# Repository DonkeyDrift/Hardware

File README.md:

# MUS4 硬件设计 - v1.0.0

> 一台能跑神经网络的小车，一个能上手的自动驾驶课堂。
>
> MUS4 面向 AI 极客、RC 车手与教育工作者，基于 DonkeyCar / 漂移驴车开源生态打造，融合 LattePanda MU 上位机算力与 ESP32 下位机控制，以纯视觉感知、云端模型训练与一键部署，让每个人都能快速搭建属于自己的端到端自动驾驶小车。

***

## 项目概述

这是 MUS4 自动驾驶小车的硬件设计仓库，包含 KiCad 格式的原理图和 PCB 布局文件。

### 硬件特性

- **LattePanda MU 主控接口**：支持上位机算力模块
- **ESP32 下位机驱动电路**：实时底层运动控制
- **摄像头、电机、舵机、传感器接口**：丰富的外设扩展
- **电源管理与电池监测电路**：安全可靠的供电系统
- **通信接口**：USB / 串口 / I2C / PWM
- **支持直接导出 Gerber 生产文件**：方便 PCB 打样

### 设计文件

| 文件名                           | 描述                |
| ----------------------------- | ----------------- |
| `DonkeyDrift-MUS4.kicad_pro`  | KiCad 项目文件        |
| `DonkeyDrift-MUS4.kicad_sch`  | 原理图文件             |
| `DonkeyDrift-MUS4.kicad_pcb`  | PCB 布局文件          |
| `Controller.kicad_sch`        | 控制器子原理图           |
| `ESP32.kicad_sch`             | ESP32 子原理图        |
| `HDMI.kicad_sch`              | HDMI 接口子原理图       |
| `Interface.kicad_sch`         | 接口子原理图            |
| `LattePanda Module.kicad_sch` | LattePanda 模块子原理图 |
| `M.2 E&amp;M Key.kicad_sch`   | M.2 接口子原理图        |
| `PSU.kicad_sch`               | 电源子原理图            |
| `USB2.0&amp;USB3.0.kicad_sch` | USB 接口子原理图        |

### 目录结构

```
Hardware/
├── BOM/              # 物料清单文件夹
├── Drill/            # 钻孔文件文件夹
├── Gerber/           # Gerber 生产文件文件夹
├── Layout/           # PCB 布局图片文件夹
├── kicad_api_libs/   # KiCad 库文件
└── [主设计文件]      # KiCad 项目、原理图、PCB 文件
```

***

## 为什么选择 MUS4

- **纯视觉端到端架构**：无需激光雷达、高精地图等昂贵传感器，仅凭摄像头即可完成感知与决策
- **双核协同，分工明确**：LattePanda MU（Ubuntu + Python）负责图像感知与模型推理，ESP32（Arduino C++）负责实时底层运动控制
- **一站式硬件平台**：自研 PCB 板打通上下位机通信，无需从零焊接飞线
- **全栈开源，社区共建**：硬件设计、软件代码、训练模型全面开源

***

## 快速开始

### 1. 查看设计文件

使用 KiCad 10.0 或更高版本打开项目文件：

```bash
# 克隆仓库
git clone <your-repo-url>
cd Hardware

# 用 KiCad 打开项目
kiCad DonkeyDrift-MUS4.kicad_pro
```

### 2. 导出 Gerber 文件

1. 在 KiCad PCB Editor 中打开 `DonkeyDrift-MUS4.kicad_pcb`
2. 点击 `File` → `Plot`
3. 选择输出格式为 Gerber
4. 配置各层输出设置
5. 点击 `Plot` 生成 Gerber 文件
6. 生成钻孔文件：`File` → `Fabrication Outputs` → `Drill Files`

### 3. 查看 BOM

物料清单位于 `BOM/` 文件夹中。

### 4. 生产文件

- Gerber 文件已导出到 `Gerber/` 文件夹
- 钻孔文件已导出到 `Drill/` 文件夹

***

## 项目架构

MUS4 硬件系统采用上下位机架构：

```
┌─────────────────────────────────────────┐
│         LattePanda MU (上位机)          │
│  - Ubuntu Linux                         │
│  - Python / OpenCV / TensorFlow         │
│  - 图像采集与模型推理                   │
└──────────────┬──────────────────────────┘
               │ USB/串口通信
┌──────────────▼──────────────────────────┐
│         ESP32 (下位机)                  │
│  - Arduino C++                          │
│  - 实时运动控制                         │
│  - 电机/舵机驱动                        │
│  - 传感器读取                           │
└──────────────┬──────────────────────────┘
               │
┌──────────────▼──────────────────────────┐
│         外设接口                         │
│  - 摄像头                               │
│  - 电机 / 舵机                          │
│  - 电池管理                             │
│  - 其他传感器                           │
└─────────────────────────────────────────┘
```

***

## 相关资源

- **主代码库**：[https://github.com/DonkeyDrift](https://github.com/DonkeyDrift/DonkeyDrift)
  - 软件库：<https://github.com/DonkeyDrift/DonkeyDrift>
  - 固件库：<https://github.com/DonkeyDrift/Firmware>
  - 硬件库：<https://github.com/DonkeyDrift/Hardware>
- **产品指南**：\[待补充]
- **3D 打印模型**：\[待补充]
- **DonkeyDrift 社区**：[donkeydrift.com](https://www.donkeydrift.com)

***

## 一台小车，七种能力

MUS4 不仅是一台自动驾驶小车，更是一套全栈式的学习平台：

- **Linux 操作系统**：系统管理、环境配置、服务部署
- **Python 编程**：图像处理、数据采集、模型推理
- **神经网络与机器学习**：端到端自动驾驶模型训练
- **计算机视觉**：OpenCV 图像处理、车道线识别
- **单片机与嵌入式开发**：ESP32 编程、Arduino C++
- **多协议处理**：USB、串口、I2C、PWM 等硬件协议
- **RC 赛车技术**：车架结构、电机调校、转向微调

***

## 开源协议（v1.1 · 分层授权）

本仓库按**客体分层授权**，自社区委员会《开源许可证分层授权决议》生效之日起适用：

| 客体 | 许可证 | 全文 |
| --- | --- | --- |
| 本仓库硬件设计文件（原理图、PCB、封装库、Gerber、钻孔、BOM、结构图、Layout 图）及其衍生实物 | **CERN Open Hardware Licence Version 2 - Permissive（CERN-OHL-P-2.0）** | [LICENSE](LICENSE) |
| 配套固件与软件（`Firmware` 仓库 MUS4_FW、上位机代码） | **Apache License 2.0** | 见 `Firmware` 仓库根目录 `LICENSE` |
| 文档与课程资料 | 逐项单独标注 | 含 CC BY-NC 等非商业限制的材料不随开源包分发，仅外链并注明 |

- **变体必须写全**：CERN-OHL-P-2.0 第 7.3 条规定，未写明变体会被默认按 CERN-OHL-S（强互惠）解释；所有对外声明一律使用 `CERN-OHL-P-2.0 / Version 2 - Permissive` 全称。
- **商标与认证**：两个协议都不授予「漂移驴车 / DonkeyDrift」名称、Logo、商标或「官方认证套件」资格，使用须经社区委员会书面批准，非官方版本须标注「非官方认证」。
- **生效边界**：Apache-2.0 授权不可撤销。此前已按 Apache-2.0 取得本设计的接收方，其已获授权不追溯变更；历史全文存档于 [LICENSE-Apache-2.0.archive.txt](LICENSE-Apache-2.0.archive.txt)。
- **版权主体与 Notice**：详见 [NOTICE.md](NOTICE.md)；最终署名以社区委员会书面决议为准。

完整发布口径与四处一致性检查见《漂移驴车-华秋开源发布准备方案》v1.1 第 4.2、4.7 节。

***

## 社区与贡献

漂移驴车社区邀请所有热爱技术、勇于创新的你加入！

- **问题反馈**：提交 Issue
- **贡献指南**：欢迎提交 Pull Request
- **联系方式**：<contact@donkeydrift.com>

***

> 因为热爱，所以极致。
>
> **漂移驴车社区，与您一同驶向智能车的未来！**

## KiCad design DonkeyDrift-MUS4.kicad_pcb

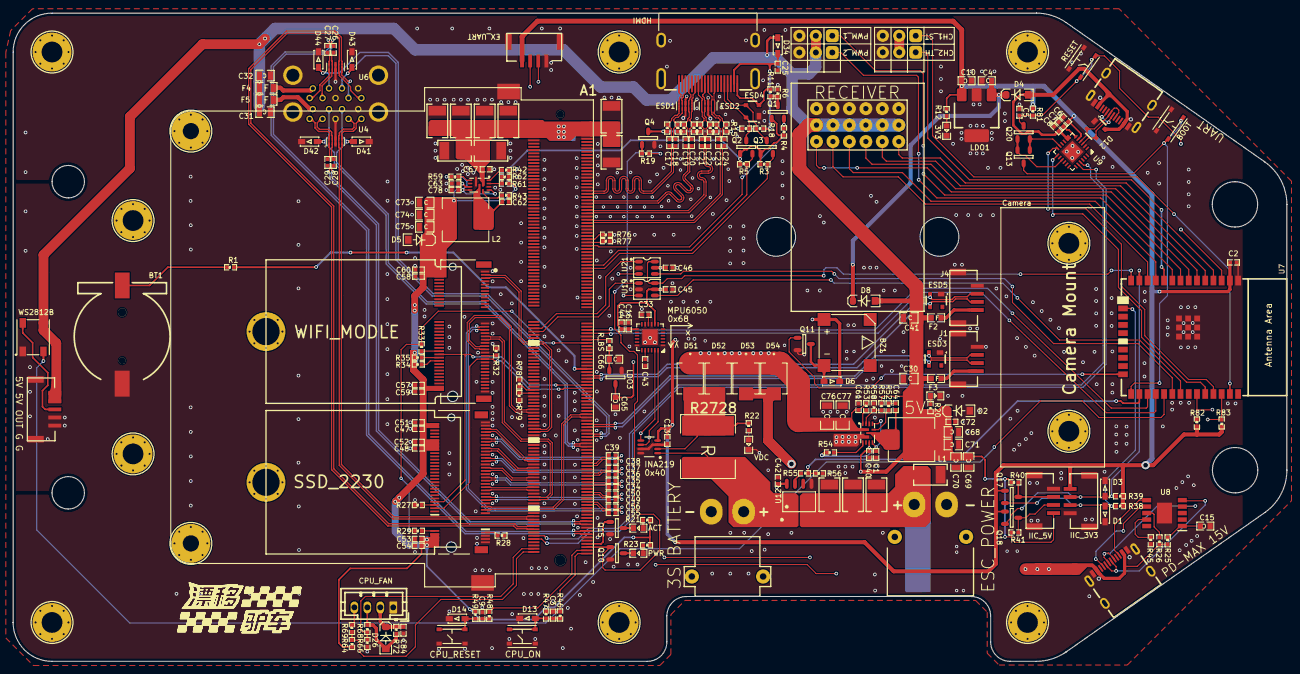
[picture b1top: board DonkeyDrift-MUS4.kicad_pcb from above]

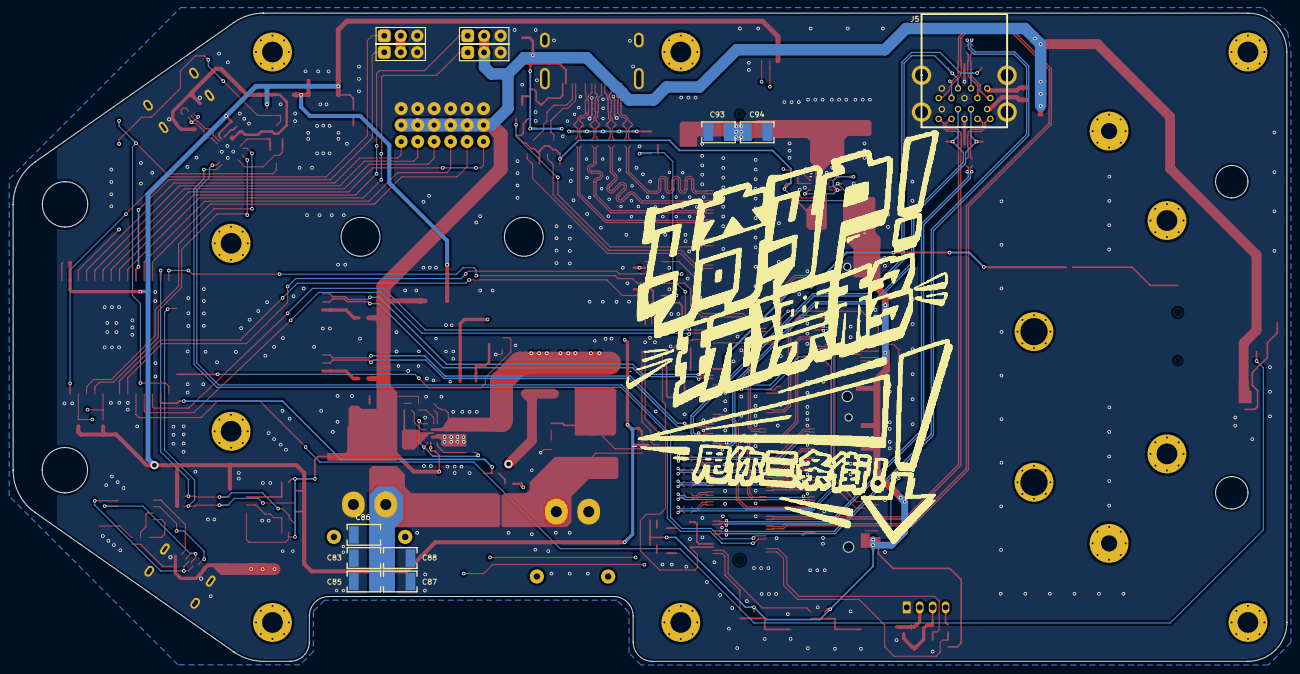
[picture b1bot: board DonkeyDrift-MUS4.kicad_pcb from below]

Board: 4 copper layers, 196.5 x 100.0 mm, 261 parts (12 on the bottom side), 198 nets.

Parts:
0x40: INA219AxD; SOT-23-8
0x68: MPU-6050; QFN-24-4X4-PAD
3S BATTERY: Conn_01x02_Pin; XT30PW-M
3V3, 5V: LED_Y; LED-0603-Y
5V 5V OUT G G: Conn_01x05_Socket; GH1.25-立-5P
A1: ASAA826-E8SB0-7H; LattePanda_Module_H8.0mm_Horizontal
ACT: LED_R; LED-0603-R
BOOT: SW_Push; SWITCH-3*4*2.5
BT1: XDCR-1220-006; Battery_Holder_CR1220_S8411-45R
BZ1: Buzzer; BEEP-MLT-8530
C1: 25V/1uf; C-0402
C2, C7, C8, C16, C17, C18, C19, C20, C21, C22, C23, C24, C25, C26, C27, C28, C29, C33, C40, C45, C46, C47, C48, C54, C59, C60, C61, C63, C67, C72, C84: 50V/100nf; C-0402
C3, C5, C6, C9, C44, C51, C52, C53, C57, C58, C78: 10V/1uf; C-0402
C4, C10: 10V/10uf; C-0603
C13, C42: 50V/100pf; C-0402
C15, C65, C66: 25V/1uf; C-0603
C30, C31, C32, C41, C68, C69, C70, C71, C73, C74, C75: 16V/22uf; C-0805
C34, C35, C36, C37, C38, C39, C49, C50, C55, C56, C62, C64: 50V/220nf; C-0402
C43: 50V/2.2nf; C-0402
C76, C77: 25V/22uf; C-1206
C80, C81, C82, C83, C85, C86, C87, C88, C89, C90, C91, C92, C93, C94, C95, C96, C97, C98, C99: 25V/47uf; C-1210
CH1_ST, CH2_TH: Conn_01x03_Socket; J-2.54-1X3
CPU_FAN: Fan_4pin; JST_PH_B4B-PH-K_1x04_P2.00mm_Vertical
CPU_ON: SW_Push; SWITCH-3*4*2.5
CPU_RESET: SW_Push; SWITCH-3*4*2.5
Camera: 摄像头; Camera Mount
D1, D3, D13, D14: ESD5V0B03; SOD-323
D2, D5: SMFJ5.0CA; SOD-123
D4, D8, D26: 1N5819WS; SOD-123
D6: 1N4148WS; SOD-323
D12: SP0503BAHT; SOT-143
D34: 1N5819WS; SOD-323
D41, D42, D43, D44: ESD-5V0B03; SOD-323
D51, D52, D53, D54: SL54B; c167b71becf44403bc24886c573a5209
DCDC1, DCDC2: MP8756GD; QFN-12-MP8756
ESC_POWER: 电调供电; XT30PW-F
ESD1, ESD2: TPAZ1023-04F; ESD-USON-10_0P5_2P5X1X0P55MM
ESD3, ESD4, ESD5: SP0503BAHT; SOT-143
EX_UART: Conn_01x04_Socket; GH1.25-立-4P
F2, F3: 6V/500mA; FUSE-0603
F4, F5: 6V/1A; FUSE-0805
FID1, FID2, FID3, FID4, FID5, FID6, FID7, FID8: Fiducial; 铜柱
HDMI: HDMI_A
IIC_3V3, IIC_5V: Conn_01x04_Socket; GH1.25-立-4P
J1, J4: Conn_01x04_Socket; GH1.25-立-4P
J5: USB3_A; USB3_A_HanElctricity
L1, L2: 3.3uH/5.2A; L-0630
LDO1: SGM2225-3.3XKC3G/TR; SOT-223-3_TabPin2
LDO3: LDO-XC6206P332MR; SOT-23-3
LOGO: LOGO-2
LOGO3: LOGO-3
PD-MAX 15V: USB_C_Receptacle_USB2.0_16P; USB-C-16P
PWM_1, PWM_2: Conn_01x03_Socket; J-2.54-1X3
PWR: LED_G; LED-0603-G
Q1, Q2, Q3, Q4, Q10, Q11, Q15, Q17, Q18: AO3400A; SOT-23-3
Q13, Q20: 2N7002; SOT-23-3
R1: 750; R-0402
R3, R5, R12, R15, R18, R19, R21, R23: 2.2K; R-0402
R4, R42, R53: 1M; R-0402
R6, R68: 21.5K; R-0402
R7, R8, R9, R10, R13, R14, R16, R17, R56: 470R; R-0402
R11: 1K; R-0402
R20, R72: 4.7K; R-0402
R22: 18K; R-0402
R25: 1K 1%; R-0402
R26: 10K 1%; R-0402
R27, R29, R32, R33: 0R; R-0402
R28, R47, R49, R64, R66: NC; R-0402
R34, R35, R78, R79, R81: 10K; R-0402
R38, R39, R82, R83: 3.3K; R-0402
R40, R41: 5.1K; R-0402
R43, R52: 3.3R; R-0402
R45: 56K 1%; R-0402
R46, R48, R69: 100R; R-0402
R54, R59, R76, R77: 100K; R-0402
R55: 680R; R-0402
R57: 41.2K; R-0402
R58: 5.6K; R-0402
R61: 43K; R-0402
R62: 9.53K; R-0402
R2728: 0.01R; R-2728
RECEIVER: RC_MODULE; RC_INTERFACE
RESET: SW_Push; SWITCH-3*4*2.5
R_BS: 10K; R-0402
SSD_2230: APCI0079-P002A; PCIE_M.2_CONNECTORS_P=0.5MM_H=4.2MM_KEYM
U4, U6: ULC0524P; ESD-USON-10_0P5_2P5X1X0P55MM
U7: ESP32-WROOM-32E-N4; ESP32-WROOM-32E
U8: CH224K; SOP100P600X180-11N
U9: CH342F; QFN-24-4X4-PAD
U12: CC6900SO; SOP-8
U19, U21: TS5A3159ADBVR; SOT-23-6
UART: USB_C_Receptacle_USB2.0_16P; USB-C-16P
VDC: LED_R; LED-0603-R
WIFI_MODLE: APCI0085-P005A; PCIE_M.2_CONNECTORS_P=0.5MM_H=4.2MM_KEYE
WS2812B: LED-WS2812B; LED-5050-4P

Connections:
5V_HDMI_VCC: C25.2, D34.1, HDMI.18, R15.2, R18.2
+3V3: 0x40.4, 0x68.8, 0x68.13, BZ1.1, C2.1, C6.2, C10.2, C13.2, C16.2, C44.2, C45.2, C46.2, D6.1, EX_UART.1, IIC_3V3.1, LDO1.3, Q17.1, Q18.1, R12.2, R38.2, R39.2, R81.2, R82.1, R83.2, U7.2, U9.5, U19.5, U21.5
+3V3C: C47.1, C48.2, C51.1, C52.1, C53.1, C54.2, C57.1, C58.1, C59.1, C60.1, R34.2, R35.2, SSD_2230.2, SSD_2230.4, SSD_2230.12, SSD_2230.14, SSD_2230.16, SSD_2230.18, SSD_2230.70, SSD_2230.72, SSD_2230.74, WIFI_MODLE.2, WIFI_MODLE.4, WIFI_MODLE.72, WIFI_MODLE.74
+5V: 5V 5V OUT G G.4, 5V 5V OUT G G.5, C30.2, C31.2, C32.2, C40.2, C41.2, C42.2, C68.2, C69.2, C70.2, C71.2, C72.2, C84.2, CPU_FAN.2, D2.1, D8.2, D26.1, D34.2, DCDC1.5, F2.1, F3.1, F4.1, F5.1, IIC_5V.1, L1.2, PWM_1.2, PWM_2.2, R20.2, R40.2, R41.2, R57.2, R72.2, RECEIVER.7, U12.8, WS2812B.1
+5V_USB: C8.2, D4.2, D12.4, U9.7, U9.8, UART.A4
+BATT: A1.115, R1.1
BEC_5V: CH1_ST.2, CH2_TH.2
BOOT: BOOT.1, Q13.3, U7.25
BZ: Q11.1, U7.24
CHIP_PU: C5.2, Q20.3, R81.1, RESET.2, U7.3
CON_PCIE_TX_0_N: C56.2, WIFI_MODLE.37
CON_PCIE_TX_0_P: C55.2, WIFI_MODLE.35
CON_PCIE_TX_1_N: C50.2, SSD_2230.47
CON_PCIE_TX_1_P: C49.2, SSD_2230.49
CON_PCIE_TX_2_N: C35.2, SSD_2230.35
CON_PCIE_TX_2_P: C34.2, SSD_2230.37
CON_PCIE_TX_3_N: C37.2, SSD_2230.23
CON_PCIE_TX_3_P: C36.2, SSD_2230.25
CON_PCIE_TX_4_N: C39.2, SSD_2230.11
CON_PCIE_TX_4_P: C38.2, SSD_2230.13
CPU_RX0: A1.12, U9.21
CPU_RX2: A1.140, U21.1
CPU_TX0: A1.10, U9.20
CPU_TX2: A1.138, U19.1
DDC_SCL: ESD4.4, HDMI.15, Q2.3, R15.1
DDC_SDA: ESD4.3, HDMI.16, Q3.3, R18.1
DDI_B_TX0_N: A1.215, C18.1
DDI_B_TX0_P: A1.217, C17.1
DDI_B_TX1_N: A1.209, C20.1
DDI_B_TX1_P: A1.211, C19.1
DDI_B_TX2_N: A1.203, C22.1
DDI_B_TX2_P: A1.205, C21.1
DDI_B_TX3_N: A1.197, C24.1
DDI_B_TX3_P: A1.199, C23.1
DTR: Q13.2, Q20.1, U9.15
EX_RX: EX_UART.3, U19.3
EX_TX: EX_UART.2, U21.3
FAN_1_PWM: A1.2, R64.1, R69.1
FAN_1_TAC: A1.4, R66.2, R68.2
GND: 0x40.3, 0x40.7, 0x40.8, 0x68.1, 0x68.9, 0x68.11, 0x68.18, 0x68.25, 3S BATTERY.2, 3V3.1, 5V.1, 5V 5V OUT G G.1, 5V 5V OUT G G.2, 5V 5V OUT G G.MP, A1.11, A1.14, A1.17, A1.20, A1.23, A1.26, A1.29, A1.32, A1.35, A1.38, A1.41, A1.44, A1.47, A1.50, A1.53, A1.56, A1.59, A1.62, A1.65, A1.68, A1.71, A1.74, A1.77, A1.80, A1.83, A1.86, A1.89, A1.92, A1.95, A1.98, A1.101, A1.107, A1.110, A1.113, A1.116, A1.135, A1.136, A1.151, A1.158, A1.167, A1.170, A1.181, A1.182, A1.188, A1.189, A1.194, A1.195, A1.200, A1.201, A1.206, A1.207, A1.212, A1.213, A1.218, A1.219, A1.224, A1.225, A1.230, A1.231, A1.236, A1.237, A1.242, A1.243, A1.248, A1.249, A1.MP, BOOT.2, BT1.2, C1.1, C2.2, C3.1, C4.1, C5.1, C6.1, C7.1, C8.1, C9.1, C10.1, C13.1, C15.1, C16.1, C25.1, C30.1, C31.1, C32.1, C33.1, C40.1, C41.1, C42.1, C43.2, C44.1, C45.1, C46.1, C47.2, C48.1, C51.2, C52.2, C53.2, C54.1, C57.2, C58.2, C59.2, C60.2, C61.1, C63.1, C65.1, C66.2, C67.1, C68.1, C69.1, C70.1, C71.1, C72.1, C73.1, C74.1, C75.1, C76.1, C77.1, C78.1, C80.1, C81.1, C82.1, C83.1, C84.1, C85.1, C86.2, C87.2, C88.2, C89.2, C90.2, C91.2, C92.2, C93.2, C94.2, C95.1, C96.1, C97.1, C98.1, C99.1, CH1_ST.3, CH2_TH.3, CPU_FAN.1, CPU_ON.2, CPU_RESET.2, D1.1, D2.2, D3.1, D5.2, D12.1, D13.1, D14.1, D41.1, D42.1, D43.1, D44.1, DCDC1.2, DCDC1.10, DCDC2.2, DCDC2.10, ESC_POWER.2, ESD1.3, ESD1.8, ESD2.3, ESD2.8, ESD3.1, ESD4.1, ESD5.1, EX_UART.4, EX_UART.MP, HDMI.2, HDMI.5, HDMI.8, HDMI.11, HDMI.17, HDMI.SH, IIC_3V3.4, IIC_3V3.MP, IIC_5V.4, IIC_5V.MP, J1.4, J1.MP, J4.4, J4.MP, J5.4, J5.7, J5.13, J5.16, J5.19, LDO1.2, LDO1.4, LDO3.1, PD-MAX 15V.A1, PD-MAX 15V.S1, PWM_1.3, PWM_2.3, Q4.2, Q10.2, Q11.2, Q15.2, R6.1, R27.2, R28.2, R32.2, R45.1, R56.1, R58.1, R62.1, R66.1, R76.1, R77.1, R78.1, R79.1, RECEIVER.8, RESET.1, SSD_2230.1, SSD_2230.3, SSD_2230.9, SSD_2230.15, SSD_2230.21, SSD_2230.27, SSD_2230.33, SSD_2230.38, SSD_2230.39, SSD_2230.45, SSD_2230.51, SSD_2230.57, SSD_2230.71, SSD_2230.73, SSD_2230.75, U4.3, U4.8, U6.3, U6.8, U7.1, U7.39, U8.11, U9.2, U9.25, U12.5, U19.2, U21.2, UART.A1, UART.S1, VDC.1, WIFI_MODLE.1, WIFI_MODLE.7, WIFI_MODLE.18, WIFI_MODLE.33, WIFI_MODLE.39, WIFI_MODLE.45, WIFI_MODLE.51, WIFI_MODLE.57, WIFI_MODLE.63, WIFI_MODLE.69, WIFI_MODLE.75, WS2812B.3
HPD: ESD4.2, HDMI.19, R11.2
ID_MOTO: R55.2, R56.2, U7.26
J1_USB_2_P5_N: A1.109, ESD5.3, J4.2
J1_USB_2_P5_P: A1.111, ESD5.2, J4.3
J4_USB_2_P3_N: A1.79, ESD3.3, J1.2
J4_USB_2_P3_P: A1.81, ESD3.2, J1.3
J5_USB3_SSRX_N: A1.18, J5.5, U6.4, U6.7
J5_USB3_SSRX_P: A1.16, J5.6, U6.5, U6.6
J5_USB3_SSTX_N: C26.2, J5.8, U6.2, U6.9
J5_USB3_SSTX_P: C27.2, J5.9, U6.1, U6.10
J5_USB_2_P2_N: A1.73, D44.2, J5.2
J5_USB_2_P2_P: A1.75, D43.2, J5.3
J6_USB4_SSRX_N: A1.24, J5.14, U4.5, U4.6
J6_USB4_SSRX_P: A1.22, J5.15, U4.4, U4.7
J6_USB4_SSTX_N: C28.2, J5.17, U4.2, U4.9
J6_USB4_SSTX_P: C29.2, J5.18, U4.1, U4.10
J6_USB_2_P1_N: A1.67, D42.2, J5.11
J6_USB_2_P1_P: A1.69, D41.2, J5.12
MCU_RX0: U7.34, U9.13
MCU_RX2: U7.31, U19.4
MCU_TX0: U7.35, U9.12
MCU_TX2: U7.30, U21.4
Net3V3_2: 3V3.2, R12.1
Net5V 5V OUT G G_3: 5V 5V OUT G G.3, WS2812B.2
Net5V_2: 5V.2, R20.1
NetA1_1: A1.1, R46.1
NetA1_3: A1.3, R48.1
NetA1_5: A1.5, Q10.1
NetA1_7: A1.7, Q15.1
NetA1_100: A1.100, R79.2
NetA1_102: A1.102, R78.2
NetA1_131: A1.131, R29.2, R33.2
NetA1_133: A1.133, R_BS.1
NetA1_137: A1.137, U7.28
NetA1_139: A1.139, U7.27
NetA1_169: A1.169, Q3.2, R3.1
NetA1_171: A1.171, Q2.2, R5.1
NetA1_183: A1.183, Q1.2, R4.1
NetA1_185: A1.185, R77.2
NetA1_187: A1.187, R76.2
NetBT1_1: BT1.1, R1.2
NetBZ1_2: BZ1.2, D6.2, Q11.3
NetC1_2: C1.2, DCDC1.6, DCDC1.9, R54.2
NetC3_2: C3.2, CPU_ON.1, D13.2, R46.2, R47.1
NetC4_2: C4.2, D4.1, D8.1, LDO1.1
NetC7_2: C7.2, U9.6
NetC9_2: C9.2, CPU_RESET.1, D14.2, R48.2, R49.1
NetC15_2: C15.2, R25.2, U8.1
NetC33_2: 0x68.10, C33.2
NetC43_1: 0x68.20, C43.1
NetC62_1: C62.1, DCDC2.7, L2.1
NetC62_2: C62.2, R43.2
NetC64_1: C64.1, DCDC1.7, L1.1
NetC64_2: C64.2, R52.2
NetC66_1: C66.1, LDO3.2, R_BS.2
NetC78_2: C78.2, DCDC2.6, DCDC2.9, R59.2
NetCH1_ST_1: CH1_ST.1, U7.37
NetCH2_TH_1: CH2_TH.1, U7.10
NetCPU_FAN_3: CPU_FAN.3, D26.2, R68.1, R72.1
NetCPU_FAN_4: CPU_FAN.4, R69.2
NetD12_2: D12.2, U9.4, UART.A7, UART.B7
NetD12_3: D12.3, U9.3, UART.A6, UART.B6
NetD53_1: D53.2, D54.2, PD-MAX 15V.A4, R25.1, R26.2
NetDCDC1_3: DCDC1.3, R54.1
NetDCDC1_8: DCDC1.8, R52.1
NetDCDC1_11: DCDC1.11, R57.1, R58.2
NetDCDC1_12: DCDC1.12, R53.1
NetDCDC2_3: DCDC2.3, R59.1
NetDCDC2_8: DCDC2.8, R43.1
NetDCDC2_11: DCDC2.11, R61.1, R62.2
NetDCDC2_12: DCDC2.12, R42.1
NetF2_2: F2.2, J4.1
NetF3_2: F3.2, J1.1
NetF4_2: F4.2, J5.1
NetF5_2: F5.2, J5.10
NetIIC_5V_2: IIC_5V.2, Q18.3, R41.1
NetIIC_5V_3: IIC_5V.3, Q17.3, R40.1
NetPD-MAX 15V_A5: PD-MAX 15V.A5, U8.7
NetPD-MAX 15V_A6: PD-MAX 15V.A6, PD-MAX 15V.B6, U8.4
NetPD-MAX 15V_A7: PD-MAX 15V.A7, PD-MAX 15V.B7, U8.5
NetPD-MAX 15V_B5: PD-MAX 15V.B5, U8.6
NetPWM_1_1: PWM_1.1, U7.8
NetPWM_2_1: PWM_2.1, U7.9
NetPWR_1: PWR.1, Q10.3
NetPWR_2: PWR.2, R23.1
NetQ1_3: Q1.3, R6.2, R11.1
NetQ4_1: Q4.1, R19.1
NetQ4_3: Q4.3, R7.1, R8.1, R9.1, R10.1, R13.1, R14.1, R16.1, R17.1
NetQ15_3: ACT.1, Q15.3
NetR21_1: ACT.2, R21.1
NetR22_1: R22.1, VDC.2
NetR26_1: R26.1, U8.8
NetR28_1: R28.1, SSD_2230.69
NetR29_1: R29.1, SSD_2230.68
NetR33_1: R33.1, WIFI_MODLE.50
NetR34_1: R34.1, WIFI_MODLE.56
NetR35_1: R35.1, WIFI_MODLE.54
NetR45_2: R45.2, U8.9
NetR55_1: R55.1, U12.7
PCIE_RX_0_N: A1.36, WIFI_MODLE.43
PCIE_RX_0_P: A1.34, WIFI_MODLE.41
PCIE_RX_1_N: A1.42, SSD_2230.41
PCIE_RX_1_P: A1.40, SSD_2230.43
PCIE_RX_2_N: A1.48, SSD_2230.29
PCIE_RX_2_P: A1.46, SSD_2230.31
PCIE_RX_3_N: A1.54, SSD_2230.17
PCIE_RX_3_P: A1.52, SSD_2230.19
PCIE_RX_4_N: A1.60, SSD_2230.5
PCIE_RX_4_P: A1.58, SSD_2230.7
PCIE_TX_0_N: A1.33, C56.1
PCIE_TX_0_P: A1.31, C55.1
PCIE_TX_1_N: A1.39, C50.1
PCIE_TX_1_P: A1.37, C49.1
PCIE_TX_2_N: A1.45, C35.1
PCIE_TX_2_P: A1.43, C34.1
PCIE_TX_3_N: A1.51, C37.1
PCIE_TX_3_P: A1.49, C36.1
PCIE_TX_4_N: A1.57, C39.1
PCIE_TX_4_P: A1.55, C38.1
PWM_IN1: RECEIVER.1, U7.4
PWM_IN2: RECEIVER.2, U7.5
PWM_IN3: RECEIVER.3, U7.6
PWM_IN4: RECEIVER.4, U7.11
PWM_IN5: RECEIVER.5, U7.12
PWM_IN6: RECEIVER.6, U7.7
REFCLKE_N: A1.90, WIFI_MODLE.49
REFCLKE_P: A1.88, WIFI_MODLE.47
REFCLKM_N: A1.87, SSD_2230.53
REFCLKM_P: A1.85, SSD_2230.55
RTS: Q13.1, Q20.2, U9.11
SCL0: 0x40.5, 0x68.23, R83.1, U7.36
SCL_3: D3.2, IIC_3V3.2, Q18.2, R39.1, U7.13
SDA0: 0x40.6, 0x68.24, R82.2, U7.33
SDA_3: D1.2, IIC_3V3.3, Q17.2, R38.1, U7.16
TMDS_CK_N: C24.2, ESD2.1, ESD2.10, HDMI.12, R7.2
TMDS_CK_P: C23.2, ESD2.2, ESD2.9, HDMI.10, R8.2
TMDS_D0_N: C22.2, ESD2.4, ESD2.7, HDMI.9, R9.2
TMDS_D0_P: C21.2, ESD2.5, ESD2.6, HDMI.7, R10.2
TMDS_D1_N: C20.2, ESD1.1, ESD1.10, HDMI.6, R13.2
TMDS_D1_P: C19.2, ESD1.2, ESD1.9, HDMI.4, R14.2
TMDS_D2_N: C18.2, ESD1.4, ESD1.7, HDMI.3, R16.2
TMDS_D2_P: C17.2, ESD1.5, ESD1.6, HDMI.1, R17.2
UART_SEL: U7.14, U19.6, U21.6
USB3_SSTX_N: A1.15, C26.1
USB3_SSTX_P: A1.13, C27.1
USB4_SSTX_N: A1.21, C28.1
USB4_SSTX_P: A1.19, C29.1
USB_2_P7_N: A1.78, WIFI_MODLE.5
USB_2_P7_P: A1.76, WIFI_MODLE.3
VCPU: A1.250, A1.251, A1.252, A1.253, A1.254, A1.255, A1.256, A1.257, A1.258, A1.259, A1.260, C61.2, C65.2, C67.2, C76.2, C77.2, C90.1, C91.1, C92.1, C93.1, C94.1, C95.2, C96.2, C97.2, C98.2, C99.2, D51.1, D52.1, D53.1, D54.1, DCDC1.1, DCDC2.1, LDO3.3, R42.2, R53.2
VDC: 0x40.2, D51.2, D52.2, R22.2, R2728.1
VIN: 0x40.1, 3S BATTERY.1, R2728.2, U12.1, U12.2
VMOTO: C80.2, C81.2, C82.2, C83.2, C85.2, C86.1, C87.1, C88.1, C89.1, ESC_POWER.1, U12.3, U12.4
WS2812: U7.29, WS2812B.4
~{CLKREQE}: R32.1, WIFI_MODLE.53
~{CLKREQM}: R27.1, SSD_2230.52
~{PLT_RST}: A1.105, SSD_2230.50, WIFI_MODLE.52
~{WAKE}: A1.103, SSD_2230.54, WIFI_MODLE.55

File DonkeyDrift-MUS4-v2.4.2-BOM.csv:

"编号";"位号";"封装";"数量";"名称";"供应商编号";
1;"C78,C6,C53,C51,C44,C58,C3,C52,C5,C9,C57";"C-0402";11;"10V/1uf";;;
2;"C48,C63,C46,C54,C72,C60,C27,C47,C22,C25,C26,C28,C17,C20,C84,C7,C29,C18,C2,C8,C33,C61,C21,C40,C45,C16,C19,C23,C59,C24,C67";"C-0402";31;"50V/100nf";;;
3;"IIC_3V3,J1,IIC_5V,J4,EX_UART";"GH1.25-立-4P";5;"Conn_01x04_Socket";;;
4;"R18,R3,R23,R21,R15,R19,R5,R12";"R-0402";8;"2.2K";;;
5;"R10,R56,R14,R17,R9,R16,R8,R7,R13";"R-0402";9;"470R";;;
6;"L2,L1";"L-0630";2;"3.3uH/5.2A";;;
7;"R78,R79,R_BS,R81,R35,R34";"R-0402";6;"10K";;;
8;"LDO1";"SOT-223-3_TabPin2";1;"SGM2225-3.3XKC3G/TR";;;
9;"0x40";"SOT-23-8";1;"INA219AxD";;;
10;"3V3,5V";"LED-0603-Y";2;"LED_Y";;;
11;"D1,D14,D3,D13";"SOD-323";4;"ESD5V0B03";;;
12;"D6";"SOD-323";1;"1N4148WS";;;
13;"Q18,Q1,Q11,Q2,Q10,Q15,Q3,Q4,Q17";"SOT-23-3";9;"AO3400A";;;
14;"U7";"ESP32-WROOM-32E";1;"ESP32-WROOM-32E-N4";;;
15;"D54,D53,D52,D51";"c167b71becf44403bc24886c573a5209";4;"SL54B";;;
16;"C4,C10";"C-0603";2;"10V/10uf";;;
17;"R45";"R-0402";1;"56K 1%";;;
18;"C75,C70,C71,C68,C74,C30,C32,C41,C31,C69,C73";"C-0805";11;"16V/22uf";;;
19;"FID2,FID1,FID8,FID3,FID7,FID6,FID4,FID5";"铜柱";8;"Fiducial";;;
20;"R59,R54,R77,R76";"R-0402";4;"100K";;;
21;"C81,C90,C82,C92,C98,C89,C95,C97,C80,C96,C91,C99,C86,C94,C88,C85,C87,C83,C93";"C-1210";19;"25V/47uf";;;
22;"R41,R40";"R-0402";2;"5.1K";;;
23;"R20,R72";"R-0402";2;"4.7K";;;
24;"CPU_FAN";"JST_PH_B4B-PH-K_1x04_P2.00mm_Vertical";1;"Fan_4pin";;;
25;"C39,C56,C62,C34,C64,C38,C49,C37,C55,C35,C50,C36";"C-0402";12;"50V/220nf";;;
26;"R2728";"R-2728";1;"0.01R";;;
27;"DCDC2,DCDC1";"QFN-12-MP8756";2;"MP8756GD";;;
28;"R29,R27,R32,R33";"R-0402";4;"0R";;;
29;"R58";"R-0402";1;"5.6K";;;
30;"R52,R43";"R-0402";2;"3.3R";;;
31;"LDO3";"SOT-23-3";1;"LDO-XC6206P332MR";;;
32;"U19,U21";"SOT-23-6";2;"TS5A3159ADBVR";;;
33;"3S BATTERY";"XT30PW-M";1;"Conn_01x02_Pin";;;
34;"U9";"QFN-24-4X4-PAD";1;"CH342F";;;
35;"D34";"SOD-323";1;"1N5819WS";;;
36;"D42,D44,D43,D41";"SOD-323";4;"ESD-5V0B03";;;
37;"F4,F5";"FUSE-0805";2;"6V/1A";;;
38;"R39,R82,R38,R83";"R-0402";4;"3.3K";;;
39;"ESD1,ESD2";"ESD-USON-10_0P5_2P5X1X0P55MM";2;"TPAZ1023-04F";;;
40;"R61";"R-0402";1;"43K";;;
41;"U6,U4";"ESD-USON-10_0P5_2P5X1X0P55MM";2;"ULC0524P";;;
42;"BT1";"Battery_Holder_CR1220_S8411-45R";1;"XDCR-1220-006";;;
43;"R55";"R-0402";1;"680R";;;
44;"R48,R46,R69";"R-0402";3;"100R";;;
45;",";"";2;"";;;
46;"R62";"R-0402";1;"9.53K";;;
47;"R57";"R-0402";1;"41.2K";;;
48;"SSD_2230";"PCIE_M.2_CONNECTORS_P=0.5MM_H=4.2MM_KEYM";1;"APCI0079-P002A";;;
49;"C77,C76";"C-1206";2;"25V/22uf";;;
50;"D2,D5";"SOD-123";2;"SMFJ5.0CA";;;
51;"BZ1";"BEEP-MLT-8530";1;"Buzzer";;;
52;"U12";"SOP-8";1;"CC6900SO";;;
53;"LOGO";"LOGO-2";1;"LOGO-2";;;
54;"0x68";"QFN-24-4X4-PAD";1;"MPU-6050";;;
55;"C66,C65,C15";"C-0603";3;"25V/1uf";;;
56;"LOGO3";"LOGO-3";1;"LOGO-3";;;
57;"UART,PD-MAX 15V";"USB-C-16P";2;"USB_C_Receptacle_USB2.0_16P";;;
58;"R53,R4,R42";"R-0402";3;"1M";;;
59;"ESD4,ESD3,D12,ESD5";"SOT-143";4;"SP0503BAHT";;;
60;"ESC_POWER";"XT30PW-F";1;"电调供电";;;
61;"F2,F3";"FUSE-0603";2;"6V/500mA";;;
62;"C42,C13";"C-0402";2;"50V/100pf";;;
63;"RESET,CPU_ON,BOOT,CPU_RESET";"SWITCH-3*4*2.5";4;"SW_Push";;;
64;"D4,D26,D8";"SOD-123";3;"1N5819WS";;;
65;"PWR";"LED-0603-G";1;"LED_G";;;
66;"R47,R66,R49,R28,R64";"R-0402";5;"NC";;;
67;"WS2812B";"LED-5050-4P";1;"LED-WS2812B";;;
68;"VDC,ACT";"LED-0603-R";2;"LED_R";;;
69;"R1";"R-0402";1;"750";;;
70;"RECEIVER";"RC_INTERFACE";1;"RC_MODULE";;;
71;"HDMI";"HDMI_A";1;"HDMI_A";;;
72;"C1";"C-0402";1;"25V/1uf";;;
73;"C43";"C-0402";1;"50V/2.2nf";;;
74;"Camera";"Camera Mount";1;"摄像头";;;
75;"Q20,Q13";"SOT-23-3";2;"2N7002";;;
76;"A1";"LattePanda_Module_H8.0mm_Horizontal";1;"ASAA826-E8SB0-7H";;;
77;"R22";"R-0402";1;"18K";;;
78;"R68,R6";"R-0402";2;"21.5K";;;
79;"5V 5V OUT G G";"GH1.25-立-5P";1;"Conn_01x05_Socket";;;
80;"R25";"R-0402";1;"1K 1%";;;
81;"R26";"R-0402";1;"10K 1%";;;
82;"WIFI_MODLE";"PCIE_M.2_CONNECTORS_P=0.5MM_H=4.2MM_KEYE";1;"APCI0085-P005A";;;
83;"U8";"SOP100P600X180-11N";1;"CH224K";;;
84;"R11";"R-0402";1;"1K";;;
85;"PWM_1,PWM_2,CH2_TH,CH1_ST";"J-2.54-1X3";4;"Conn_01x03_Socket";;;
86;"J5";"USB3_A_HanElctricity";1;"USB3_A";;;
